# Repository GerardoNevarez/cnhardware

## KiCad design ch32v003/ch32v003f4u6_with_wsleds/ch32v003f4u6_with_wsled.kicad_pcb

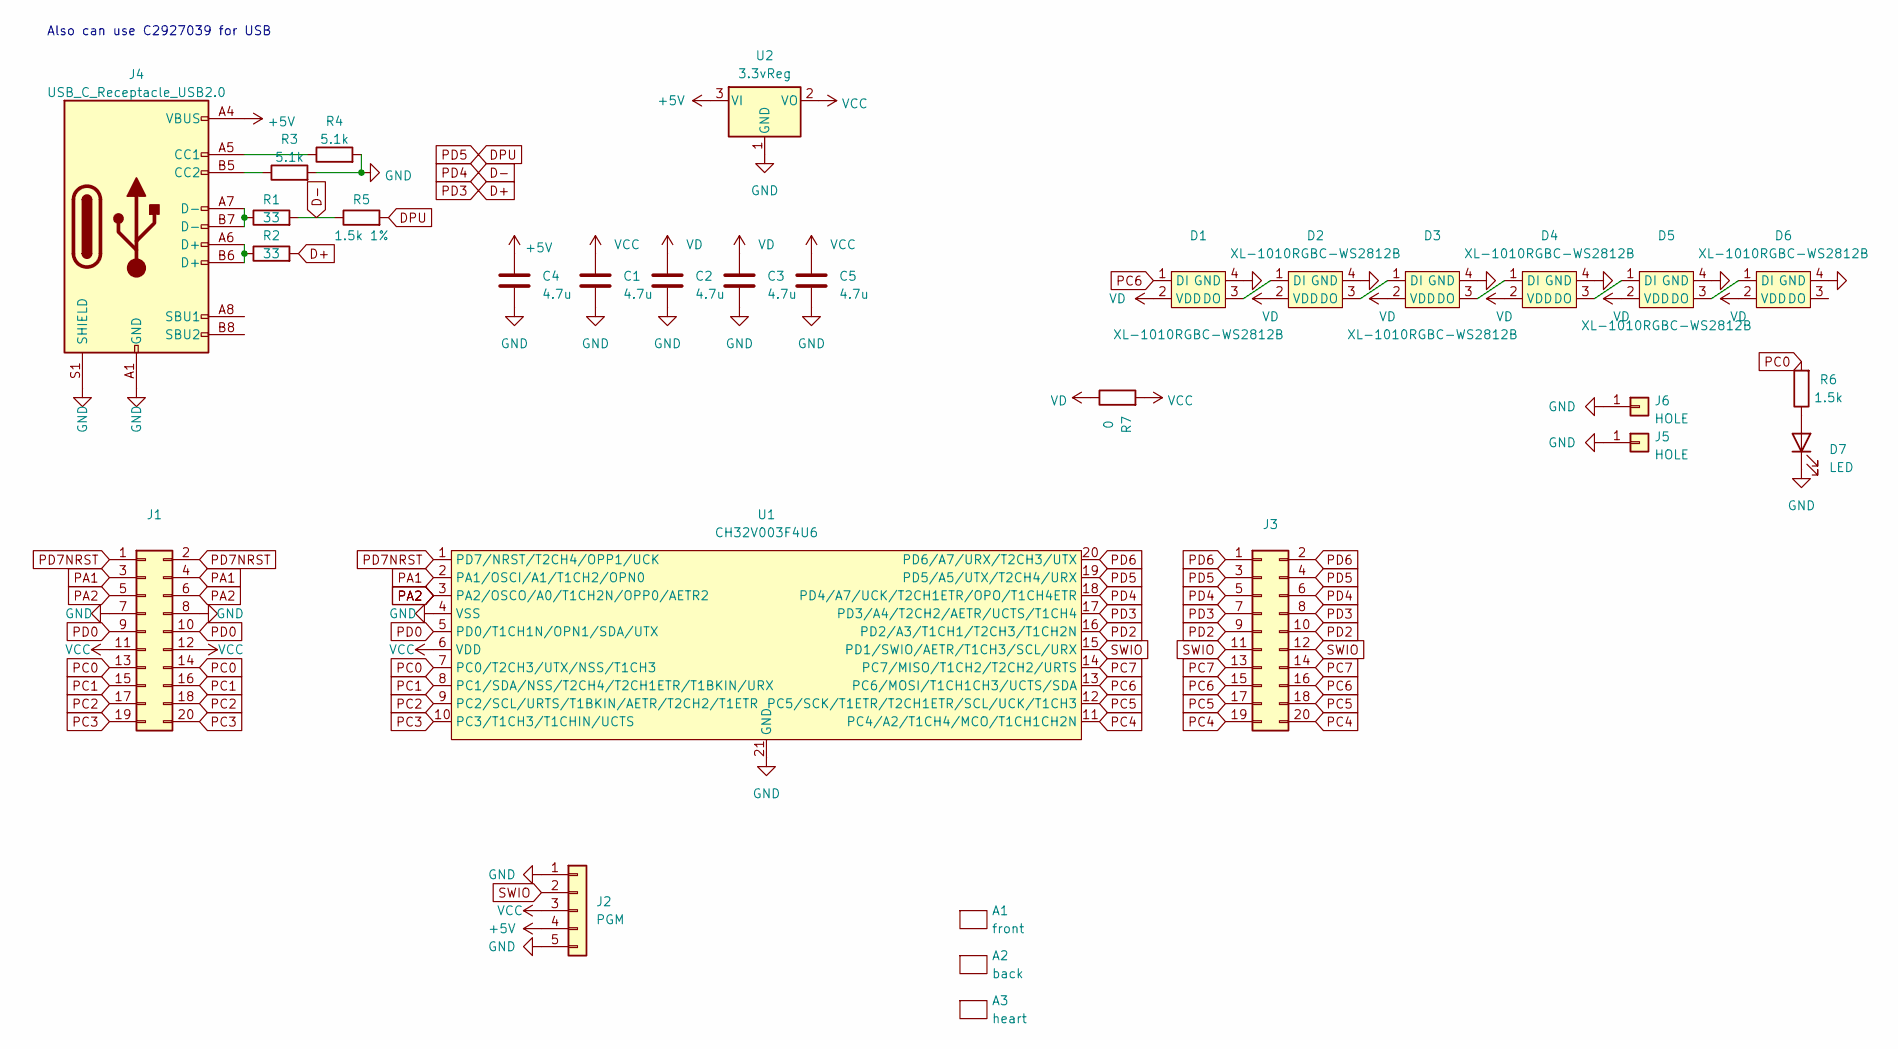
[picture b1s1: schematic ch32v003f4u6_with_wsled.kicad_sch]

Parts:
A1: front; Front
A2: back; Back
A3: heart; Heart
C1, C2, C3, C4, C5: 4.7u; C_0402_1005Metric; LCSC C23733
D1, D2, D3, D4, D5, D6: XL-1010RGBC-WS2812B; XL-1010RGBC-WS812B; LCSC C5349953
D7: LED; LED_0805_2012Metric; LCSC C34499
J1, J3: PinHeader_2x10_P2.54mm_Vertical; LCSC C124359
J2: PGM; PinHeader_1x05_P2.54mm_Vertical; LCSC C358687
J4: USB_C_Receptacle_USB2.0; USB_C_Receptacle_HRO_TYPE-C-31-M-12; LCSC C709358
J5, J6: HOLE; MountingHole_2.2mm_M2_DIN965_Pad
R1, R2: 33; R_0402_1005Metric; LCSC C25105
R3, R4: 5.1k; R_0402_1005Metric; LCSC C25905
R5: 1.5k 1%; R_0402_1005Metric; LCSC C25867
R6: 1.5k; R_0402_1005Metric; LCSC C25867
R7: 0; R_0402_1005Metric; LCSC C17168
U1: CH32V003F4U6; QFN-20-1EP_3x3mm_P0.4mm_EP1.65x1.65mm; LCSC C5299908
U2: 3.3vReg; SOT-23-3; LCSC C5446

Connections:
+5V: C4.1, J2.4, J4.A4 (VBUS), J4.A9 (VBUS), J4.B4 (VBUS), J4.B9 (VBUS), U2.3 (VI)
D+: J3.7, J3.8, R2.2, U1.17 (PD3/A4/T2CH2/AETR/UCTS/T1CH4)
D-: J3.5, J3.6, R1.2, R5.1, U1.18 (PD4/A7/UCK/T2CH1ETR/OPO/T1CH4ETR)
DPU: J3.3, J3.4, R5.2, U1.19 (PD5/A5/UTX/T2CH4/URX)
GND: C1.2, C2.2, C3.2, C4.2, C5.2, D1.4 (GND), D2.4 (GND), D3.4 (GND), D4.4 (GND), D5.4 (GND), D6.4 (GND), D7.1 (K), J1.7, J1.8, J2.1, J2.5, J4.A1 (GND), J4.A12 (GND), J4.B1 (GND), J4.B12 (GND), J4.S1 (SHIELD), J5.1, J6.1, R3.2, R4.2, U1.4 (VSS), U1.21 (GND), U2.1 (GND)
unnamed: D1.3 (DO), D2.1 (DI)
unnamed: D2.3 (DO), D3.1 (DI)
unnamed: D3.3 (DO), D4.1 (DI)
unnamed: D4.3 (DO), D5.1 (DI)
unnamed: D5.3 (DO), D6.1 (DI)
unnamed: D7.2 (A), R6.1
unnamed: J4.A5 (CC1), R4.1
unnamed: J4.B5 (CC2), R3.1
unnamed: J4.A6 (D+), J4.B6 (D+), R2.1
unnamed: J4.A7 (D-), J4.B7 (D-), R1.1
PA1: J1.3, J1.4, U1.2 (PA1/OSCI/A1/T1CH2/OPN0)
PA2: J1.5, J1.6, U1.3 (PA2/OSCO/A0/T1CH2N/OPP0/AETR2)
PC0: J1.13, J1.14, R6.2, U1.7 (PC0/T2CH3/UTX/NSS/T1CH3)
PC1: J1.15, J1.16, U1.8 (PC1/SDA/NSS/T2CH4/T2CH1ETR/T1BKIN/URX)
PC2: J1.17, J1.18, U1.9 (PC2/SCL/URTS/T1BKIN/AETR/T2CH2/T1ETR)
PC3: J1.19, J1.20, U1.10 (PC3/T1CH3/T1CHIN/UCTS)
PC4: J3.19, J3.20, U1.11 (PC4/A2/T1CH4/MCO/T1CH1CH2N)
PC5: J3.17, J3.18, U1.12 (PC5/SCK/T1ETR/T2CH1ETR/SCL/UCK/T1CH3)
PC6: D1.1 (DI), J3.15, J3.16, U1.13 (PC6/MOSI/T1CH1CH3/UCTS/SDA)
PC7: J3.13, J3.14, U1.14 (PC7/MISO/T1CH2/T2CH2/URTS)
PD0: J1.9, J1.10, U1.5 (PD0/T1CH1N/OPN1/SDA/UTX)
PD2: J3.9, J3.10, U1.16 (PD2/A3/T1CH1/T2CH3/T1CH2N)
PD6: J3.1, J3.2, U1.20 (PD6/A7/URX/T2CH3/UTX)
PD7NRST: J1.1, J1.2, U1.1 (PD7/NRST/T2CH4/OPP1/UCK)
SWIO: J2.2, J3.11, J3.12, U1.15 (PD1/SWIO/AETR/T1CH3/SCL/URX)
VCC: C1.1, C5.1, J1.11, J1.12, J2.3, R7.2, U1.6 (VDD), U2.2 (VO)
VD: C2.1, C3.1, D1.2 (VDD), D2.2 (VDD), D3.2 (VDD), D4.2 (VDD), D5.2 (VDD), D6.2 (VDD), R7.1

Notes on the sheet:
Also can use C2927039 for USB

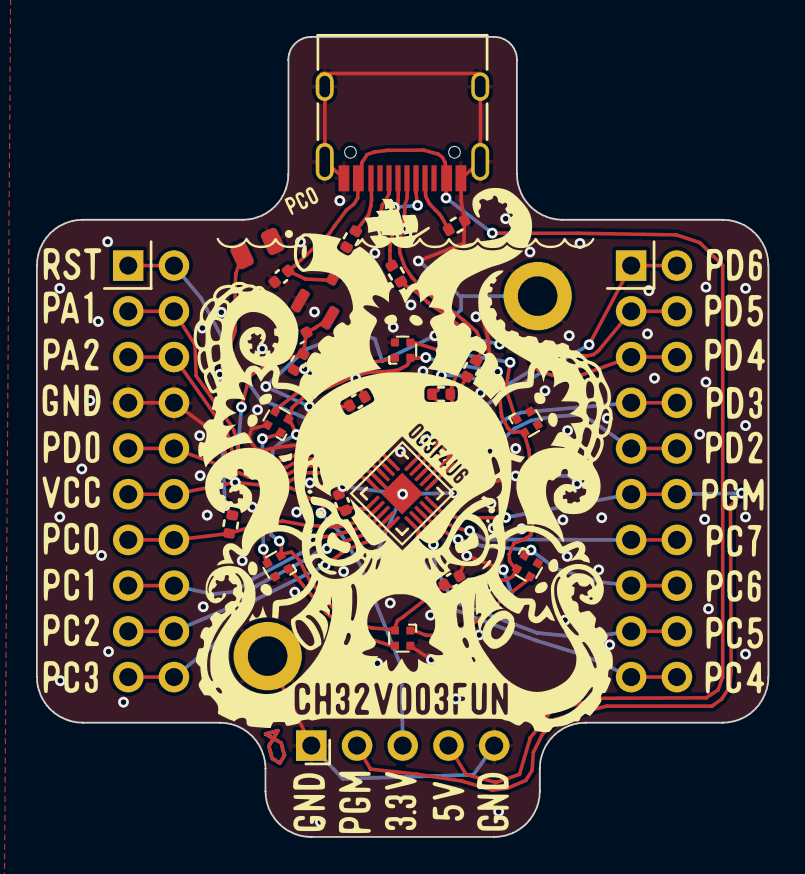
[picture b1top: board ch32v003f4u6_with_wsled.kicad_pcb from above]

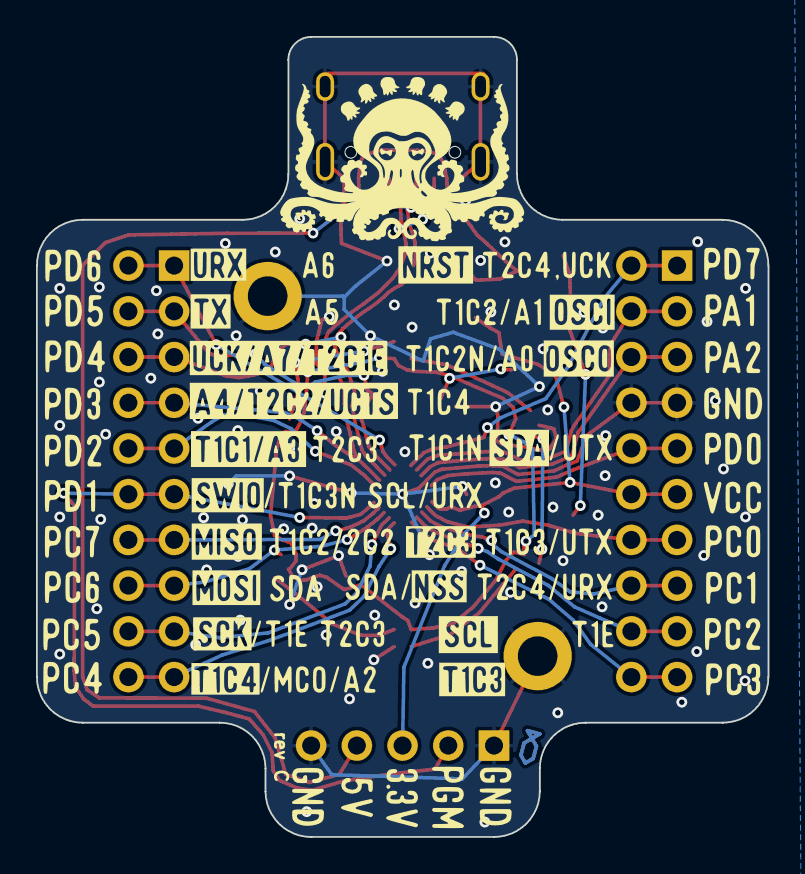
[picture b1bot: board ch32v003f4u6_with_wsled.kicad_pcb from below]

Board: 2 copper layers, 40.6 x 44.5 mm, 30 parts (2 on the bottom side), 32 nets.

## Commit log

2023-06-04 Replace some components with basic parts
